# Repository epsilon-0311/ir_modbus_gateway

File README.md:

# ir_modbus_gateway
ESP8266 ModBus TCP to Infrared Gateway

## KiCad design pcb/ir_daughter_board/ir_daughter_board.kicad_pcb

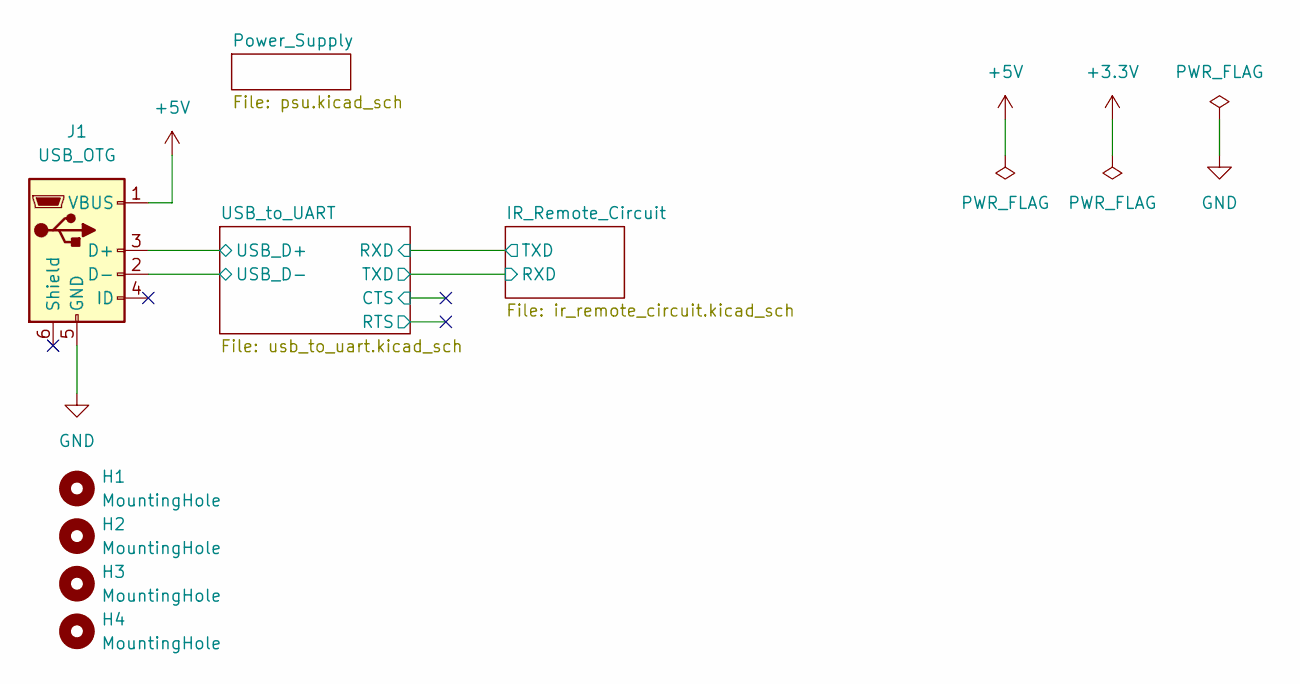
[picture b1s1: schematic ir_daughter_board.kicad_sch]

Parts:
H1, H2, H3, H4: MountingHole; MountingHole_3.2mm_M3
J1: USB_OTG; USB_Micro-AB_Molex_47590-0001

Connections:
+5V: J1.1 (VBUS); also elsewhere on the board
/USB_to_UART/USB_D+: J1.3 (D+); also elsewhere on the board
/USB_to_UART/USB_D-: J1.2 (D-); also elsewhere on the board
GND: J1.5 (GND); also elsewhere on the board

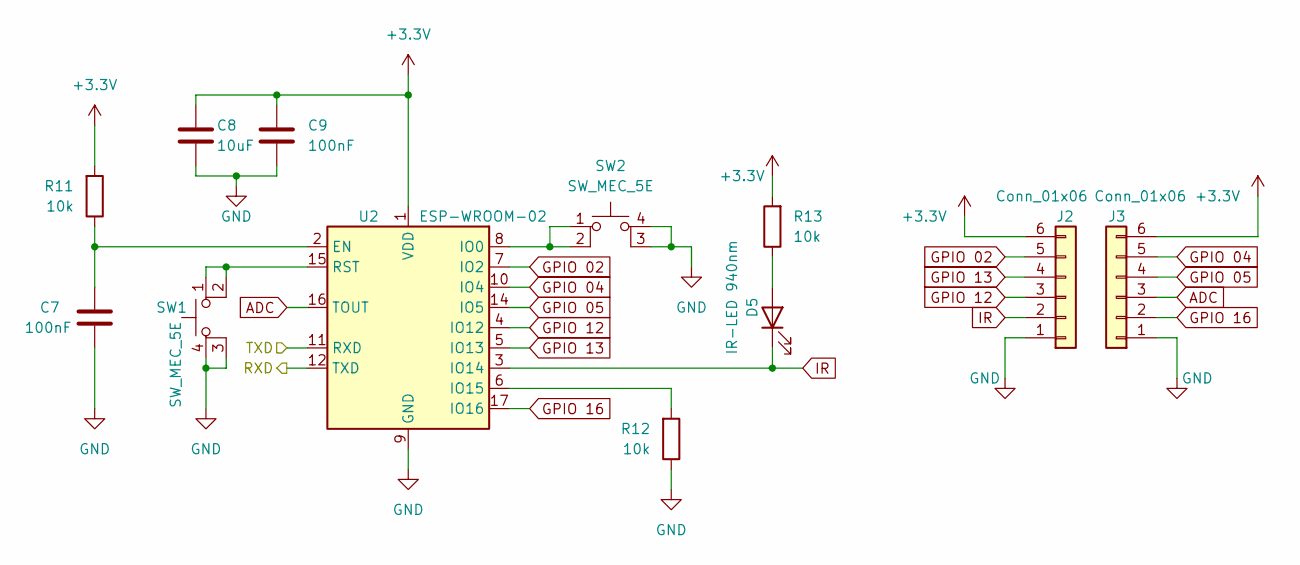
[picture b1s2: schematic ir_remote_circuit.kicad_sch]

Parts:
C7, C9: 100nF; C_0603_1608Metric
C8: 10uF; C_0603_1608Metric
D5: IR-LED 940nm; LED_D5.0mm
J2, J3: Conn_01x06; PinHeader_1x06_P2.54mm_Vertical
R11, R12, R13: 10k; R_0603_1608Metric
SW1, SW2: SW_MEC_5E; SW_SPST_Omron_B3FS-100xP
U2: ESP-WROOM-02

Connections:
+3V3: C8.1, C9.1, J2.6, J3.6, R11.2, R13.2, U2.1 (VDD); also elsewhere on the board
/IR_Remote_Circuit/RXD: U2.12 (TXD); also elsewhere on the board
/IR_Remote_Circuit/TXD: U2.11 (RXD); also elsewhere on the board
ADC: J3.3, U2.16 (TOUT)
GND: C7.2, C8.2, C9.2, J2.1, J3.1, R12.1, SW1.3 (K), SW1.4 (A), SW2.3 (K), SW2.4 (A), U2.9 (GND), U2.13 (GND), U2.18 (GND), U2.19 (GND); also elsewhere on the board
GPIO 02: J2.5, U2.7 (IO2)
GPIO 04: J3.5, U2.10 (IO4)
GPIO 05: J3.4, U2.14 (IO5)
GPIO 12: J2.3, U2.4 (IO12)
GPIO 13: J2.4, U2.5 (IO13)
GPIO 16: J3.2, U2.17 (IO16)
IR: D5.1 (K), J2.2, U2.3 (IO14)
unnamed: C7.1, R11.1, U2.2 (EN)
unnamed: D5.2 (A), R13.1
unnamed: R12.2, U2.6 (IO15)
unnamed: SW1.1, SW1.2, U2.15 (RST)
unnamed: SW2.1, SW2.2, U2.8 (IO0)

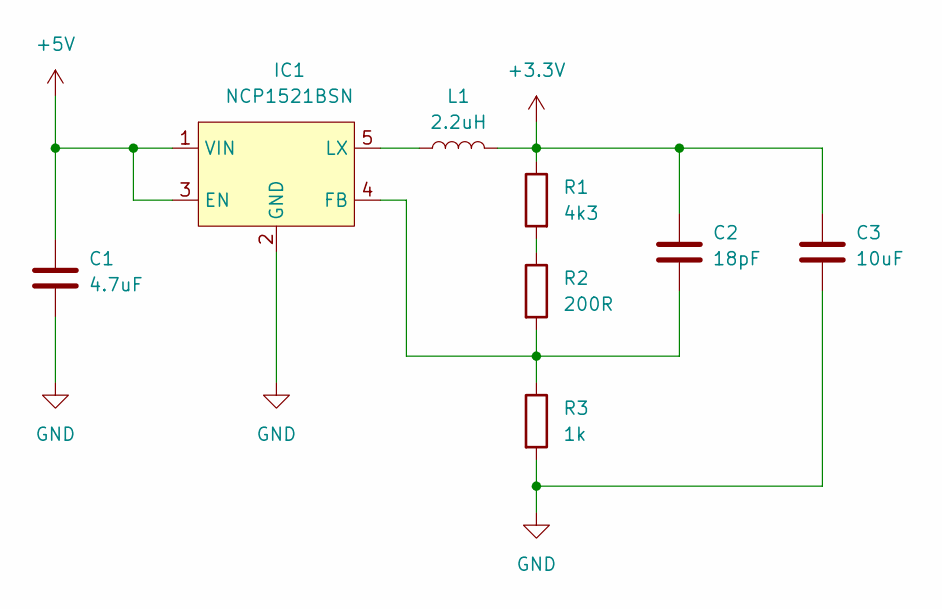
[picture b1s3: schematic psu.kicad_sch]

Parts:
C1: 4.7uF; C_1210_3225Metric
C2: 18pF; C_0603_1608Metric
C3: 10uF; C_0603_1608Metric
IC1: NCP1521BSN; TSOP-5_1.65x3.05mm_P0.95mm
L1: 2.2uH; L_1210_3225Metric
R1: 4k3; R_0603_1608Metric
R2: 200R; R_0603_1608Metric
R3: 1k; R_0603_1608Metric

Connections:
+3V3: C2.1, C3.1, L1.2, R1.1; also elsewhere on the board
+5V: C1.1, IC1.1 (VIN), IC1.3 (EN); also elsewhere on the board
GND: C1.2, C3.2, IC1.2 (GND), R3.2; also elsewhere on the board
unnamed: C2.2, IC1.4 (FB), R2.2, R3.1
unnamed: IC1.5 (LX), L1.1
unnamed: R1.2, R2.1

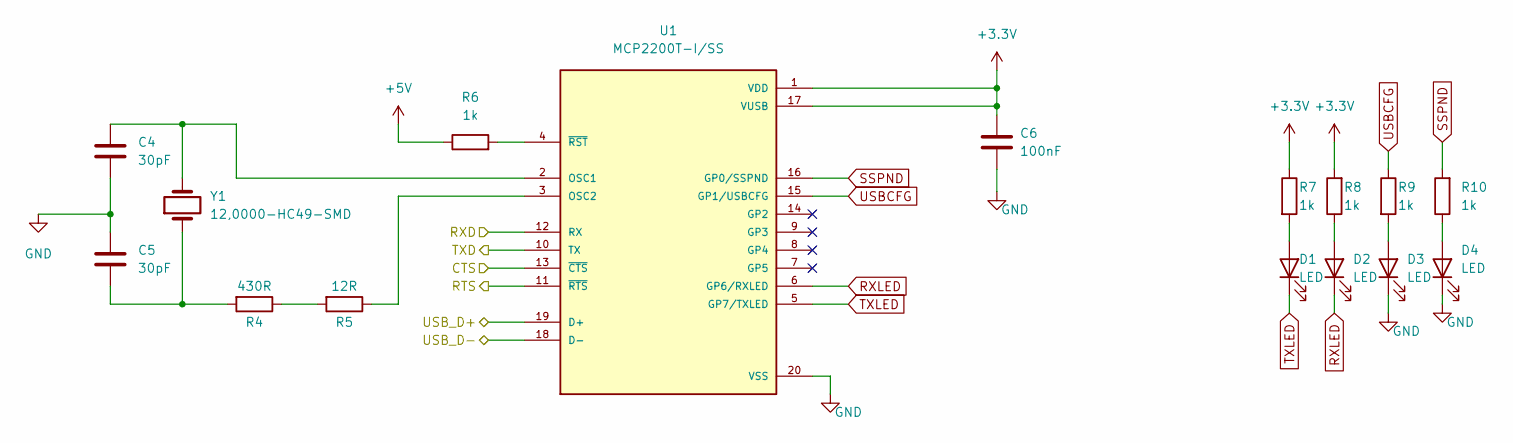
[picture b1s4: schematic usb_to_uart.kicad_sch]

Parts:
C4, C5: 30pF; C_0603_1608Metric
C6: 100nF; C_0603_1608Metric
D1, D2, D3, D4: LED; LED_0603_1608Metric
R4: 430R; R_0603_1608Metric
R5: 12R; R_0603_1608Metric
R6, R7, R8, R9, R10: 1k; R_0603_1608Metric
U1: MCP2200T-I/SS; SSOP-20_5.3x7.2mm_P0.65mm; PARTREV D
Y1: 12,0000-HC49-SMD; Crystal_SMD_HC49-SD_HandSoldering

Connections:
+3V3: C6.1, R7.1, R8.2, U1.1 (VDD), U1.17 (VUSB); also elsewhere on the board
+5V: R6.1; also elsewhere on the board
/IR_Remote_Circuit/RXD: U1.10 (TX); also elsewhere on the board
/IR_Remote_Circuit/TXD: U1.12 (RX); also elsewhere on the board
/USB_to_UART/CTS: U1.13 (~CTS)
/USB_to_UART/RTS: U1.11 (~RTS)
/USB_to_UART/USB_D+: U1.19 (D+); also elsewhere on the board
/USB_to_UART/USB_D-: U1.18 (D-); also elsewhere on the board
GND: C4.2, C5.1, C6.2, D3.1 (K), D4.1 (K), U1.20 (VSS); also elsewhere on the board
unnamed: C4.1, U1.2 (OSC1), Y1.2
unnamed: D1.2 (A), R7.2
unnamed: D2.2 (A), R8.1
unnamed: D3.2 (A), R9.2
unnamed: D4.2 (A), R10.1
unnamed: C5.2, R4.2, Y1.1
unnamed: R5.1, U1.3 (OSC2)
unnamed: R4.1, R5.2
unnamed: R6.2, U1.4 (~RST)
RXLED: D2.1 (K), U1.6 (GP6/RXLED)
SSPND: R10.2, U1.16 (GP0/SSPND)
TXLED: D1.1 (K), U1.5 (GP7/TXLED)
USBCFG: R9.1, U1.15 (GP1/USBCFG)

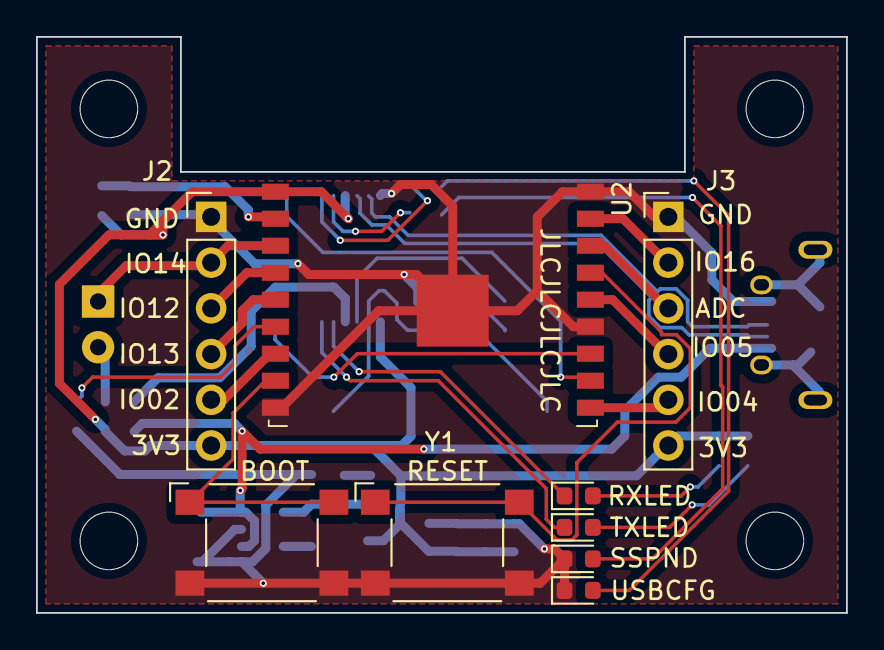
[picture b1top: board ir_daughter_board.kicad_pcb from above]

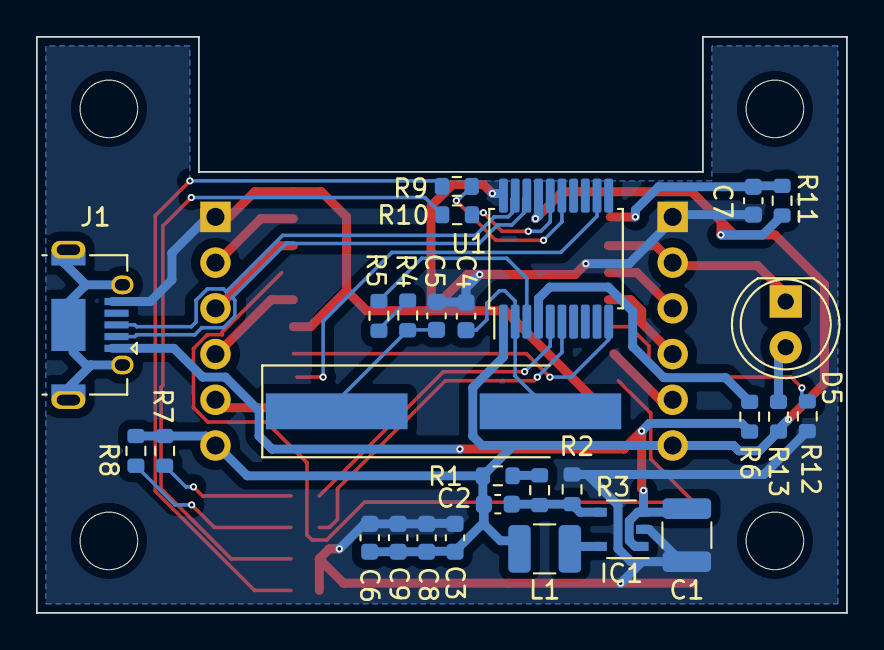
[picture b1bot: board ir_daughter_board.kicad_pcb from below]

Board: 2 copper layers, 45.0 x 32.0 mm, 41 parts (28 on the bottom side), 36 nets.

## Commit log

2021-10-16 added implementation of modbus server and sending of IR Remote raw sending
2021-10-23 added commands for beamer
2021-10-23 added usage of NEC and EPSON commands, implemented usage of new commands
2022-01-07 added pcb
2022-01-07 minor editorial changes
2022-01-09 refined circuit with reddit comments
2022-01-11 removed backups
2022-01-11 updated schematic
2022-01-11 removed unused footprints and symbols
2022-01-13 change MCP2200 footprint to standard footprint
2022-01-15 minor update in PCB
2022-01-15 updated exports
2022-01-15 adapted pcb due to parts availability
2022-01-16 minor updateds in references and values
